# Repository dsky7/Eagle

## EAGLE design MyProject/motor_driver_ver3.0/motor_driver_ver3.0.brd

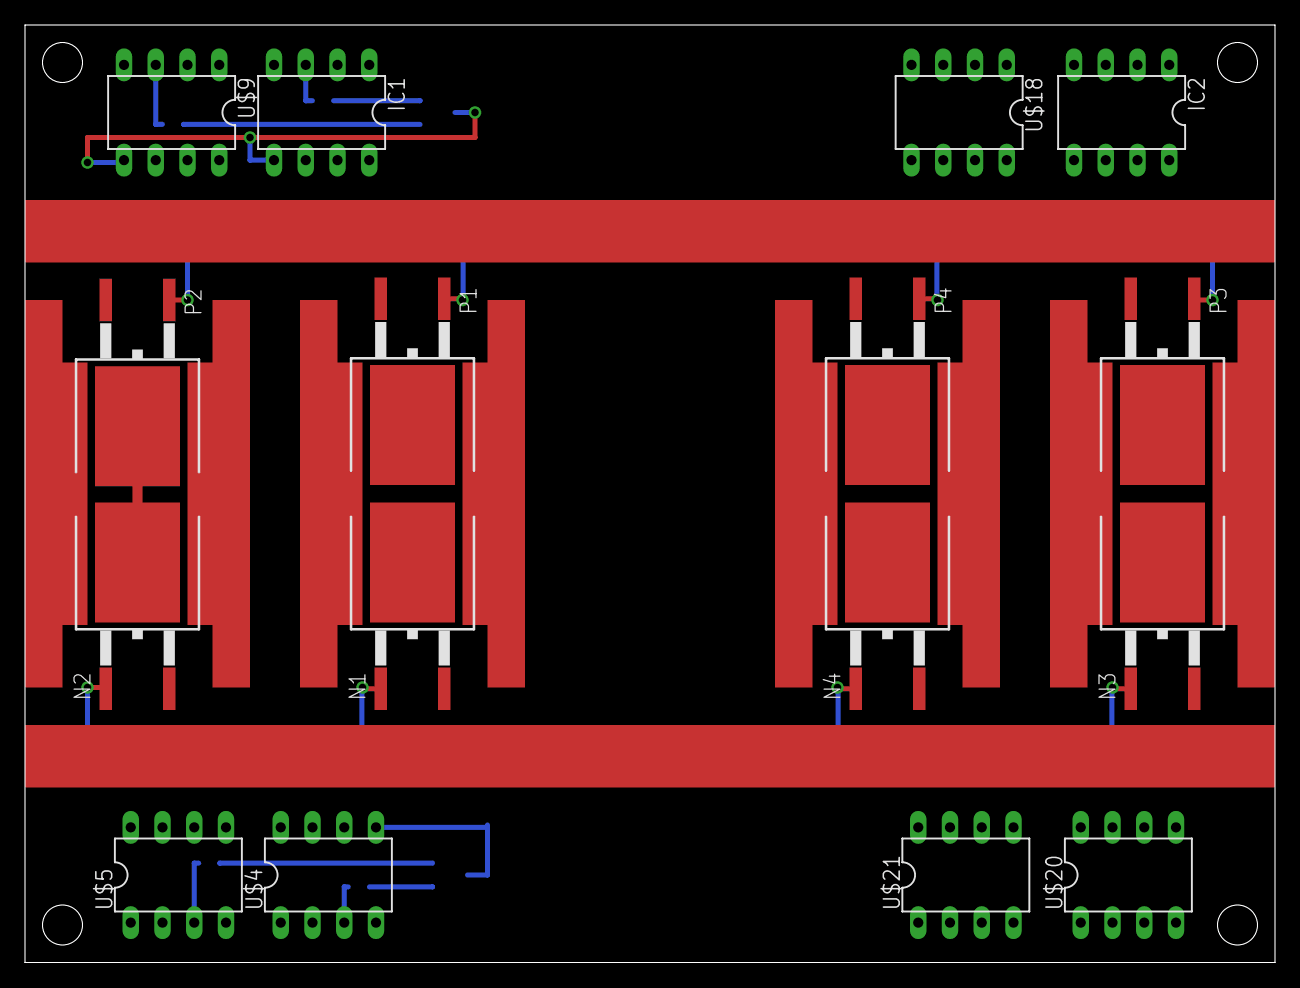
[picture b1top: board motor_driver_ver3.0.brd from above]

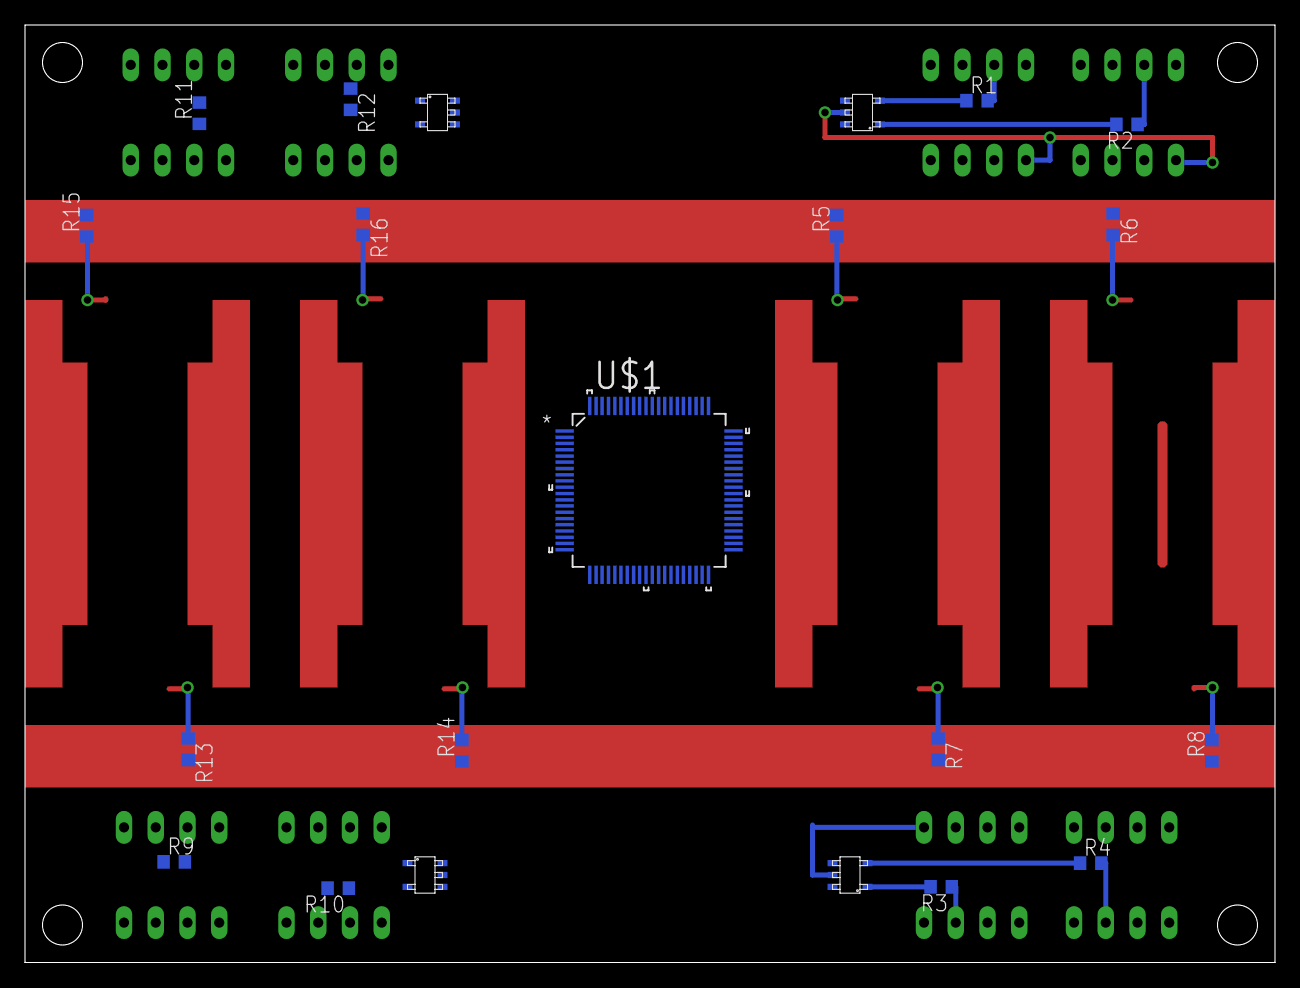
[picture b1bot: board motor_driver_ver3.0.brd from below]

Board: 2 copper layers, 100.0 x 75.0 mm, 37 parts (21 on the bottom side), 43 nets.

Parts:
IC1, IC2: TLP351; DIL08
N1, N2, N3, N4: FDB8441; TO-263
P1, P2, P3, P4: SUM110P06; TO-263
R1, R2, R3, R4, R5, R6, R7, R8, R9, R10, R11, R12, R13, R14, R15, R16: RESISTOR__SMD; 1608
U$1: DSPIC33FJ64MC508IP; QFP50P1400X1400X120-80N
U$4, U$5, U$9, U$18, U$20, U$21: TLP351; DIL08
U$8, U$14, U$15, U$19: CPH5617; CHP-5

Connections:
+5V: IC1.2, IC2.2, U$4.2, U$5.2, U$9.2, U$18.2, U$20.2, U$21.2
+16.8V: IC1.8, IC2.8, P1.2, P2.2, P3.2, P4.2, U$4.8, U$5.8, U$9.8, U$18.8, U$20.8, U$21.8
GND: IC1.5, IC2.5, N1.2, N2.2, N3.2, N4.2, U$4.5, U$5.5, U$8.4, U$9.5, U$14.4, U$15.4, U$18.5, U$19.4, U$20.5, U$21.5
unnamed: R4.1, U$14.2
unnamed: R3.2, U$14.1
unnamed: R3.1, U$4.3
unnamed: R4.2, U$5.3
unnamed: U$1.76, U$14.3
unnamed: U$1.78, U$14.5
unnamed: R1.1, U$19.2
unnamed: R2.2, U$19.1
unnamed: N1.1, R7.1
unnamed: N2.1, R8.2
unnamed: R7.2, U$4.6
unnamed: N1.3, P1.3
unnamed: N2.3, P2.3
unnamed: R8.1, U$5.6
unnamed: P1.1, R5.1
unnamed: IC1.6, R5.2
unnamed: IC1.3, R1.2
unnamed: R2.1, U$9.3
unnamed: U$1.79, U$19.5
unnamed: U$1.77, U$19.3
unnamed: P2.1, R6.2
unnamed: R6.1, U$9.6
unnamed: N3.3, P3.3
unnamed: N4.3, P4.3
unnamed: R9.1, U$20.3
unnamed: R10.2, U$21.3
unnamed: IC2.3, R11.2
unnamed: R12.1, U$18.3
unnamed: R10.1, U$8.2
unnamed: R9.2, U$8.1
unnamed: R11.1, U$15.2
unnamed: R12.2, U$15.1
unnamed: N3.1, R13.1
unnamed: R13.2, U$20.6
unnamed: N4.1, R14.2
unnamed: R14.1, U$21.6
unnamed: P3.1, R15.1
unnamed: IC2.6, R15.2
unnamed: P4.1, R16.2
unnamed: R16.1, U$18.6

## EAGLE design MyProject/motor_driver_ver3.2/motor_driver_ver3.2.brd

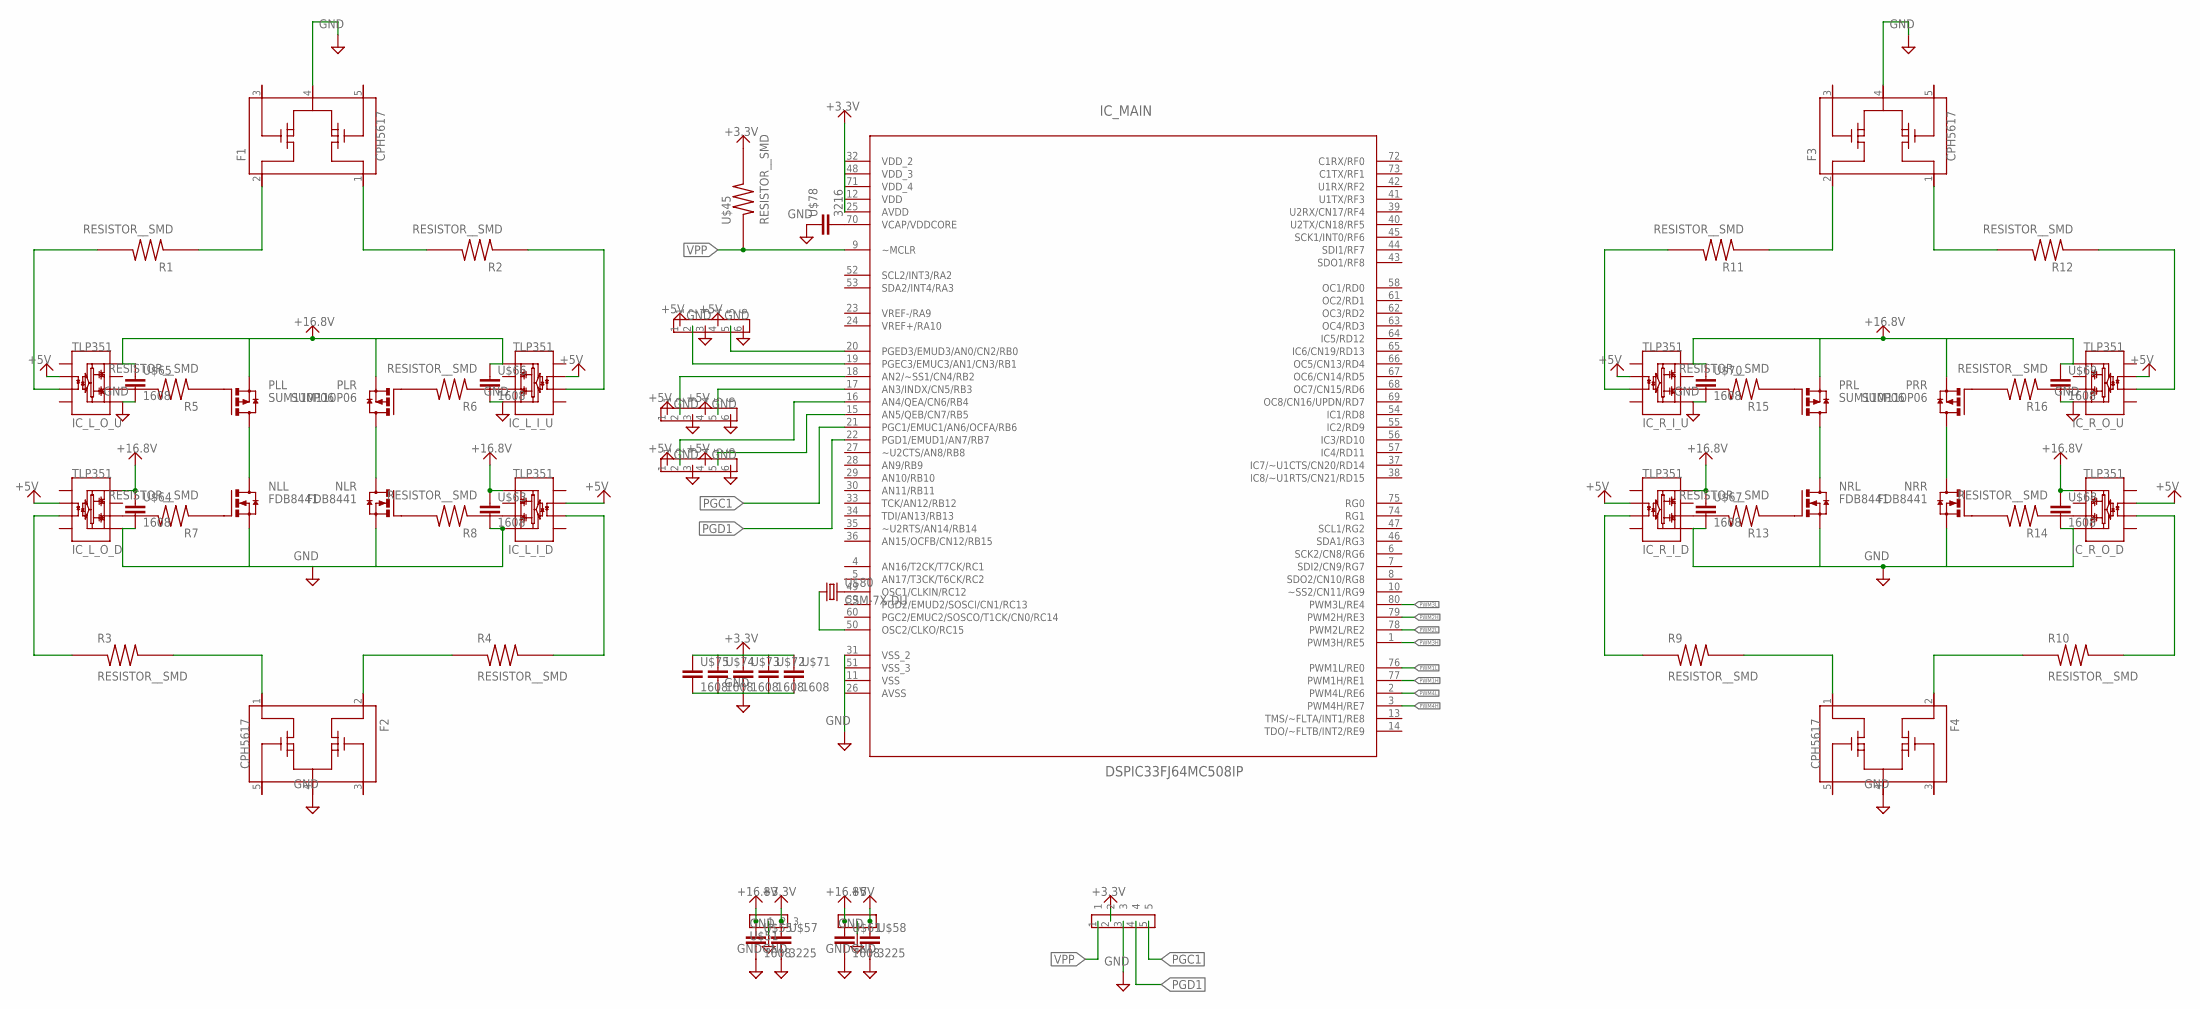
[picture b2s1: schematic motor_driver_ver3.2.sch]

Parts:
F1, F2, F3, F4: CPH5617; CHP-5
IC_L_I_D: TLP351; DIL08
IC_L_I_U: TLP351; DIL08
IC_L_O_D: TLP351; DIL08
IC_L_O_U: TLP351; DIL08
IC_MAIN: DSPIC33FJ64MC508IP; QFP50P1400X1400X120-80N
IC_R_I_D: TLP351; DIL08
IC_R_I_U: TLP351; DIL08
IC_R_O_D: TLP351; DIL08
IC_R_O_U: TLP351; DIL08
NLL: FDB8441; TO-263
NLR: FDB8441; TO-263
NRL: FDB8441; TO-263
NRR: FDB8441; TO-263
PLL: SUM110P06; TO-263
PLR: SUM110P06; TO-263
PRL: SUM110P06; TO-263
PRR: SUM110P06; TO-263
R1, R2, R3, R4, R5, R6, R7, R8, R9, R10, R11, R12, R13, R14, R15, R16: RESISTOR__SMD; 1608
U$1: PIN_HEADER_5
U$4, U$5, U$20: PIN_HEADER_6
U$45: RESISTOR__SMD; 1608
U$47: TA48M05; ＨＳＩＰ３
U$51: TA48M033; ＨＳＩＰ３
U$55, U$61, U$63, U$64, U$65, U$66, U$67, U$68, U$69, U$70, U$71, U$72, U$73, U$74, U$75: 1608
U$57, U$58: 3225
U$78: 3216
U$80: CSM-7X-DU

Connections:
+3.3V: IC_MAIN.12 (VDD), IC_MAIN.25 (AVDD), IC_MAIN.32 (VDD_2), IC_MAIN.48 (VDD_3), IC_MAIN.71 (VDD_4), U$1.2, U$45.2, U$51.3, U$57.P$1 (1), U$71.P$1 (1), U$72.P$1 (1), U$73.P$1 (1), U$74.P$1 (1), U$75.P$1 (1)
+5V: IC_L_I_D.2 (LED+), IC_L_I_U.2 (LED+), IC_L_O_D.2 (LED+), IC_L_O_U.2 (LED+), IC_R_I_D.2 (LED+), IC_R_I_U.2 (LED+), IC_R_O_D.2 (LED+), IC_R_O_U.2 (LED+), U$4.1, U$4.4, U$5.1, U$5.4, U$20.1, U$20.4, U$47.3 (OUT), U$58.P$1 (1)
+16.8V: IC_L_I_D.8 (VDD), IC_L_I_U.8 (VDD), IC_L_O_D.8 (VDD), IC_L_O_U.8 (VDD), IC_R_I_D.8 (VDD), IC_R_I_U.8 (VDD), IC_R_O_D.8 (VDD), IC_R_O_U.8 (VDD), PLL.2 (S), PLR.2 (S), PRL.2 (S), PRR.2 (S), U$47.1 (IN), U$51.1, U$55.P$1 (1), U$61.P$1 (1), U$63.P$1 (1), U$64.P$1 (1), U$65.P$1 (1), U$66.P$1 (1), U$67.P$1 (1), U$68.P$1 (1), U$69.P$1 (1), U$70.P$1 (1)
GND: F1.4 (S), F2.4 (S), F3.4 (S), F4.4 (S), IC_L_I_D.5 (GND), IC_L_I_U.5 (GND), IC_L_O_D.5 (GND), IC_L_O_U.5 (GND), IC_MAIN.11 (VSS), IC_MAIN.26 (AVSS), IC_MAIN.31 (VSS_2), IC_MAIN.51 (VSS_3), IC_R_I_D.5 (GND), IC_R_I_U.5 (GND), IC_R_O_D.5 (GND), IC_R_O_U.5 (GND), NLL.2 (S), NLR.2 (S), NRL.2 (S), NRR.2 (S), U$1.3, U$4.3, U$4.6, U$5.3, U$5.6, U$20.3, U$20.6, U$47.2 (GND), U$51.2, U$55.P$2 (2), U$57.P$2 (2), U$58.P$2 (2), U$61.P$2 (2), U$63.P$2 (2), U$64.P$2 (2), U$65.P$2 (2), U$66.P$2 (2), U$67.P$2 (2), U$68.P$2 (2), U$69.P$2 (2), U$70.P$2 (2), U$71.P$2 (2), U$72.P$2 (2), U$73.P$2 (2), U$74.P$2 (2), U$75.P$2 (2), U$78.P$1 (1)
unnamed: F2.2 (D2), R4.1
unnamed: F2.1 (D1), R3.2
unnamed: IC_L_O_D.3 (LED-), R3.1
unnamed: IC_L_I_D.3 (LED-), R4.2
unnamed: IC_MAIN.19 (PGEC3/EMUC3/AN1/CN3/RB1), U$4.2
unnamed: IC_MAIN.49 (OSC1/CLKIN/RC12), U$80.2
unnamed: F1.2 (D2), R1.1
unnamed: F1.1 (D1), R2.2
unnamed: NLL.1 (G), R7.1
unnamed: NLR.1 (G), R8.2
unnamed: IC_L_O_D.6 (OUT), R7.2
unnamed: NLL.3 (D), PLL.3 (D)
unnamed: NLR.3 (D), PLR.3 (D)
unnamed: IC_L_I_D.6 (OUT), R8.1
unnamed: PLL.1 (G), R5.1
unnamed: IC_L_O_U.6 (OUT), R5.2
unnamed: IC_L_O_U.3 (LED-), R1.2
unnamed: IC_L_I_U.3 (LED-), R2.1
unnamed: IC_MAIN.20 (PGED3/EMUD3/AN0/CN2/RB0), U$4.5
unnamed: IC_MAIN.18 (AN2/~SS1/CN4/RB2), U$5.2
unnamed: PLR.1 (G), R6.2
unnamed: IC_L_I_U.6 (OUT), R6.1
unnamed: NRL.3 (D), PRL.3 (D)
unnamed: NRR.3 (D), PRR.3 (D)
unnamed: IC_R_I_D.3 (LED-), R9.1
unnamed: IC_R_O_D.3 (LED-), R10.2
unnamed: IC_MAIN.17 (AN3/INDX/CN5/RB3), U$5.5
unnamed: IC_MAIN.16 (AN4/QEA/CN6/RB4), U$20.2
unnamed: IC_R_I_U.3 (LED-), R11.2
unnamed: IC_R_O_U.3 (LED-), R12.1
unnamed: IC_MAIN.15 (AN5/QEB/CN7/RB5), U$20.5
unnamed: IC_MAIN.50 (OSC2/CLKO/RC15), U$80.1
unnamed: F4.2 (D2), R10.1
unnamed: F4.1 (D1), R9.2
unnamed: F3.2 (D2), R11.1
unnamed: F3.1 (D1), R12.2
unnamed: NRL.1 (G), R13.1
unnamed: IC_R_I_D.6 (OUT), R13.2
unnamed: NRR.1 (G), R14.2
unnamed: IC_R_O_D.6 (OUT), R14.1
unnamed: PRL.1 (G), R15.1
unnamed: IC_R_I_U.6 (OUT), R15.2
unnamed: PRR.1 (G), R16.2
unnamed: IC_R_O_U.6 (OUT), R16.1
unnamed: IC_MAIN.70 (VCAP/VDDCORE), U$78.P$2 (2)
PGC1: IC_MAIN.21 (PGC1/EMUC1/AN6/OCFA/RB6), U$1.5
PGD1: IC_MAIN.22 (PGD1/EMUD1/AN7/RB7), U$1.4
PWM1H: IC_MAIN.77 (PWM1H/RE1)
PWM1L: IC_MAIN.76 (PWM1L/RE0)
PWM2H: IC_MAIN.79 (PWM2H/RE3)
PWM2L: IC_MAIN.78 (PWM2L/RE2)
PWM3H: IC_MAIN.1 (PWM3H/RE5)
PWM3L: IC_MAIN.80 (PWM3L/RE4)
PWM4H: IC_MAIN.3 (PWM4H/RE7)
PWM4L: IC_MAIN.2 (PWM4L/RE6)
VPP: IC_MAIN.9 (~MCLR), U$1.1, U$45.1

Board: 2 copper layers, 63 parts (0 on the bottom side), 52 nets, no tracks yet.

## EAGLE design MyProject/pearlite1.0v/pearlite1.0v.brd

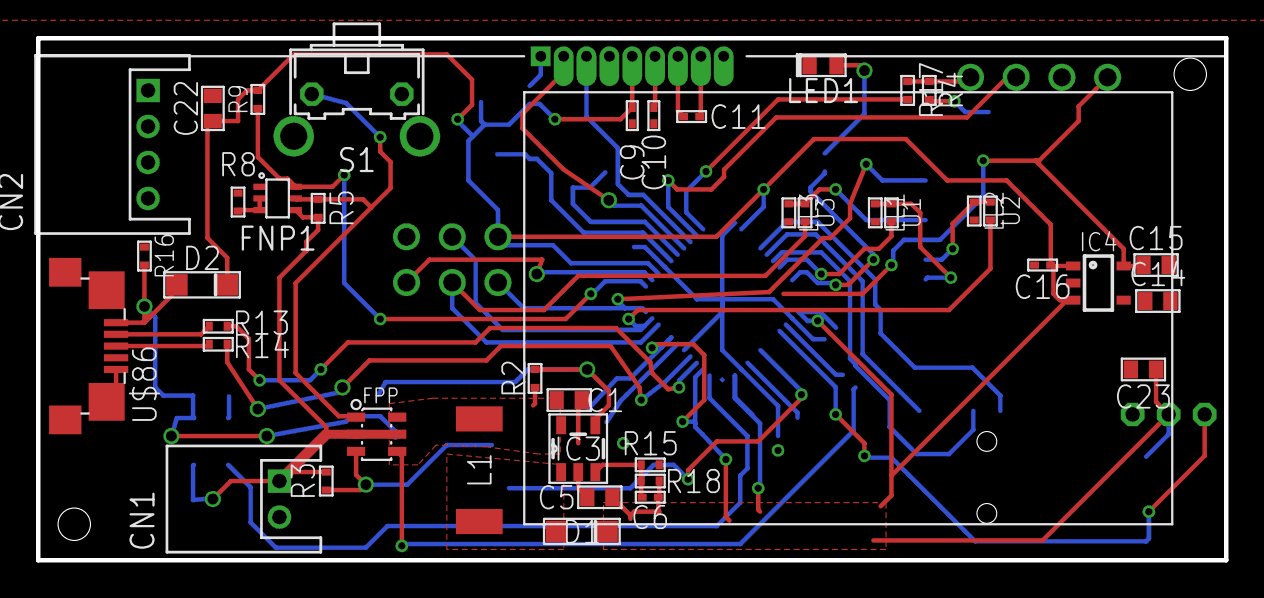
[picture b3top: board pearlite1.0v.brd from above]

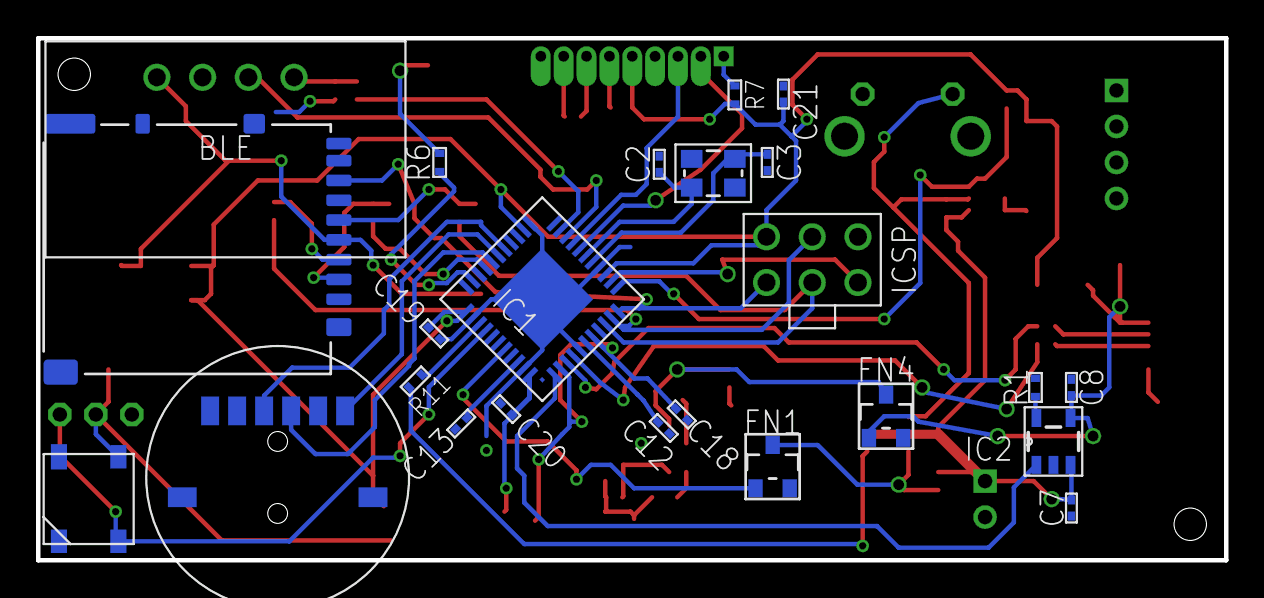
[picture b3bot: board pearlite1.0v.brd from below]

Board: 2 copper layers, 66.0 x 29.0 mm, 68 parts (24 on the bottom side), 49 nets.

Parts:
BLE: BLE_SERIAL2_NO_HOLE; BLESERIAL2_NO_HOLE
C1, C5: 22uF; 1608
C2, C3: 10pF; 1005
C6: 1nF; 1005
C7, C8: 4.7uF; 1005
C9, C10, C11: 1005
C12, C16: 1uF; 1005
C13, C18, C19, C20, C21: 0.1uF; 1005
C14: 0.01uF; 1608
C15, C23: 10uF; 1608
C22: 47uF; 1608
CN1: S2B-PH-K-S
CN2: S4B-PH-K-S
D1, D2: SOD-123; SOD_123
FN1, FN4: CHIP_FET; SOT23
FNP1: SI1553CDL; SOT363
FPP: FDC6506P; SOT23-6
IC1: ATMEGA32U4; QFN-44-7X7
IC2: MCP73831; SOT23-5L
IC3: LM2735; SOT23-5L
IC4: TAR5SB; SSOP5-P-0.95
L1: D63; TOKO
LED1: CHIPLED; 1608
LED2: NEO_FLAT
LL1: 3k; 1005
LL2, LL3: 3K; 1005
R1: 2K; 1005
R2: 100K; 1005
R3, R5, R8, R9, R15, R16: 10K; 1005
R4: 1.5k; 1005
R6: 330; 1005
R7: RESISTOR_1005; 1005
R11, R17: 1K; 1005
R13, R14: 22; 1005
R18: 30k; 1005
S1: B3F-31XX
U1, U3: 2K; 1005
U2: 2k; 1005
U$3: ICSP
U$8: LIPO400MAH
U$30: 3PIN_HALF; 3PIN_INT_HALF
U$45: DM3AT-SF-PEJ
U$68: LCD_I2C_AQM; AQM1602
U$86: MICRO-USB-KYORITU; ZX62R-B-5P
U$90: TMHU28
XTAL: FA-238

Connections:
+3.3V: BLE.4, C15.P$1, IC4.5, U$45.4
+3.7V: C1.P$1, FPP.4, FPP.6, IC3.5, L1.1, R2.2, R11.2
+5V: C5.P$1, C6.1, C9.1, C16.1, C18.1, C19.1, C20.1, C21.1, C22.P$1, C23.P$1, D1.C, D2.C, IC1.2, IC1.7, IC1.14, IC1.24, IC1.34, IC1.44, IC4.1, IC4.3, LED2.1, R7.2, R9.2, R18.2, U$3.2, U$30.2, U$68.P$5
+USB5V: C8.1, D2.A, FN4.1, IC2.4, R16.2, U$86.5
A1: IC1.37, LED2.4, U$30.3
A4: FN1.1, IC1.40
ADC0: IC1.36, R11.1
ATOM: BLE.1, R4.2, R17.1
D0: BLE.2, IC1.20
D1: IC1.21, R17.2
D2: IC1.19, U$68.P$3
D3: IC1.18, U$68.P$2
D6: IC1.27, U$90.3
D7: IC1.1, IC2.1
D8: IC1.28, U$90.1
D9: IC1.29, U$90.T
D10: IC1.30, U1.2
D11: FNP1.6, IC1.12, R9.1
D13: IC1.32, R6.2
D+: R14.2, U$86.3
D-: R13.2, U$86.4
DL: D1.A, IC3.1, L1.2
FB: C6.2, IC3.3, R15.2, R18.1
GND: BLE.3, C1.P$2, C2.2, C3.2, C5.P$2, C7.2, C8.2, C9.2, C10.2, C12.1, C13.2, C14.P$2, C15.P$2, C16.2, C18.2, C19.2, C20.2, C21.2, C22.P$2, C23.P$2, CN1.2, FN1.2, FN4.2, FNP1.1, IC1.5, IC1.15, IC1.23, IC1.35, IC1.43, IC1.TH, IC2.2, IC3.2, IC4.2, LED1.2, LED2.3, LL1.2, LL2.2, LL3.2, R1.1, R4.1, R8.1, R15.1, R16.1, S1.1, U$3.6, U$30.1, U$45.6, U$45.GND1, U$45.GND2, U$45.GND3, U$45.GND4, U$68.P$4, U$86.1, U$86.M1, U$86.M2, U$86.M3, U$86.M4, U$90.C, XTAL.2, XTAL.4
MISO: IC1.11, U$3.1, U$45.7
MOSI: IC1.10, U2.2, U$3.4
unnamed: LED1.1, R6.1
unnamed: IC2.5, R1.2
unnamed: FN4.3, IC3.4, R2.1
unnamed: R7.1, U$68.P$1
unnamed: LL3.1, U3.1, U$45.5
unnamed: FN1.3, FPP.3, R3.1
unnamed: C3.1, IC1.16, XTAL.1
unnamed: IC1.3, R13.1
unnamed: C13.1, IC1.42
unnamed: C2.1, IC1.17, XTAL.3
unnamed: LL2.1, U2.1, U$45.3
unnamed: LL1.1, U1.1, U$45.2
unnamed: C12.2, IC1.6
unnamed: IC1.4, R14.1
unnamed: C14.P$1, IC4.4
unnamed: C10.1, U$68.P$6
unnamed: C11.1, U$68.P$7
unnamed: C11.2, U$68.P$8
RESET: IC1.13, U$3.5
SCLK: IC1.9, U3.2, U$3.3
SIG: FNP1.2, FNP1.3, R8.2
SWSIG: FNP1.5, FPP.1, R5.1, S1.2
V2: C7.1, CN1.1, FNP1.4, FPP.2, FPP.5, IC2.3, R3.2, R5.2

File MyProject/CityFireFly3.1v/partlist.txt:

Partlist

Exported from CityFireFly_3.1v.brd at 2016/03/04 19:21

EAGLE Version 7.5.0 Copyright (c) 1988-2015 CadSoft

Assembly variant: 

Part     Value               Package            Library      Position (mm)         Orientation

BLE      BLE_SERIAL2_NO_HOLE BLESERIAL2_NO_HOLE 12_module    (30 5)                MR0
C1       22uF                1608               02_C         (25.5 13.1)           MR180
C2       10pF                1005               02_C         (43.7 3.9)            MR270
C3       10pF                1005               02_C         (49.5 3.9)            MR90
C5       22uF                1608               02_C         (27.2 18.5)           MR0
C6       1nF                 1005               02_C         (30 18.4)             MR0
C7       4.7uF               1005               02_C         (12.4 13.9)           R270
C8       4.7uF               1005               02_C         (15.2 14)             R180
C12      1uF                 1005               02_C         (43.45 18.85)         R0
C13      0.1uF               1005               02_C         (37 16.7)             MR45
C14      0.01uF              1608               02_C         (23.45 7.8)           R180
C15      10uF                1608               02_C         (23.4 5.9)            R180
C16      1uF                 1005               02_C         (29.1 7.3)            R270
C18      0.1uF               1005               02_C         (38.35 5.1)           MR225
C19      0.1uF               1005               02_C         (38.7 16.7)           MR315
C20      0.1uF               1005               02_C         (35 12.7)             MR135
C21      0.1uF               1005               02_C         (46.8 7.4)            MR270
C22      47uF                1608               02_C         (3.5 5.6)             MR0
C23      10uF                1608               02_C         (56.5 16)             MR180
CN1                          JST-PH2            jst-ph (1)   (9.4 16.1)            MR0
D1       SOD-123             SOD_123            15_DIODE     (26.2 20.4)           MR180
D2       SOD-123             SOD_123            15_DIODE     (12.3 6)              R180
FN1      CHIP_FET            SOT23              06_FET       (13.8 7.9)            MR0
FN4      CHIP_FET            SOT23              06_FET       (21.6 16.7)           R0
FNP1     SI1553CDL           SOT363             06_FET       (33.8 7)              R270
FPP      FDC6506P            SOT23-6            06_FET       (13.8 15.1)           MR90
IC1      ATMEGA32U4          QFN-44-7X7         04_IC        (40.5 11)             MR315
IC2      MCP73831            SOT23-5L           04_IC        (15.1 16.5)           R270
IC3      LM2735              SOT23-5L           04_IC        (26 15.8)             MR180
IC4      TAR5SB              SSOP5-P-0.95       04_IC        (26.7 6.9)            R90
L1       D63                 TOKO               03_L         (20.3 17)             MR90
LED1     3MMLED              3MM                10_LED       (27 11)               R90
LED2     NEO_FLAT            NEO_FLAT           10_LED       (56.5 11)             MR270
LED3     NEO_FLAT            NEO_FLAT           10_LED       (3.5 11)              MR90
R1       2K                  1005               01_R         (17.6 17)             R90
R2       100K                1005               01_R         (25.7 16.1)           R270
R3       10K                 1005               01_R         (11 13.9)             MR90
R4       1.5k                1005               01_R         (37.1 3.2)            MR180
R5       10K                 1005               01_R         (36.25 6.35)          R270
R6       330                 1005               01_R         (29.6 9.4)            MR180
R8       10K                 1005               01_R         (31.9 6.8)            R270
R9       10K                 1005               01_R         (34.8 5.8)            MR225
R11      1K                  1005               01_R         (34.8 14.7)           MR45
R13      22                  1005               01_R         (40.7 17.1)           R180
R14      22                  1005               01_R         (40.7 16.2)           R180
R15      10K                 1005               01_R         (30 16.8)             MR0
R16      10K                 1005               01_R         (20.5 3.4)            R270
R17      1K                  1005               01_R         (41 3.2)              R0
R18      30k                 1005               01_R         (30 17.6)             MR180
SW2      SKRPACE010          SKRP               09_1_switch  (41 11)               R270
U$3      ICSP                ICSP               08_CONECTOR  (49.3 16)             MR90
USB      USB_MICRO_VERTICAL  USB_MICRO_VERTICAL 08_CONECTOR  (19 11)               R0
XTAL     FA-238              FA-238             09_2_CRYSTAL (46.5 4.5)            MR0
